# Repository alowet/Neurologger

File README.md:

## WILD: Wireless, Interactive, Lightweight Datalogger 

**WILD** (Wireless, Interactive, Lightweight Datalogger) is an open-source platform for **wireless, closed-loop electrophysiology and behavior monitoring** in freely moving small animals. It integrates high-density electrophysiology, optogenetic stimulation, an inertial measurement unit (IMU), ultrasonic microphone, and head-mounted camera into a lightweight system for **multi-modal recording**.

---

## 📌 Overview

- High-density neural recording  
- BLE-based wireless control and real-time monitoring  
- Closed-loop stimulation with DSP filtering and thresholds  
- SD-card logging in CE32 format with efficient data export  
- Windows GUI for device setup, live visualization, and data download  

---

## 📖 Documentation

Full documentation can be found here:

- [Installation](docs/install.md)  
- [Hardware](docs/hardware.md)
- [Usage Guide](docs/usage.md)  
- [Closed-loop Control](docs/closed-loop.md)
- [TinyML(Under development for supporting user-compiled models)](docs/tinyML.md)
- [File Format](docs/file-format.md)  
- [Development](docs/development.md)  

---

## 🖥 Quick start guide
WILD system board

Connector definitions

WILD system diagram

### Device manufacturing
- PCB manufacturing and assembly (Gerber + BOM provided)
[Download here](https://github.com/ayalab1/Neurologger/tree/main/PCB)  
- Recommended PCB manufacturer: [NextPCB](https://www.nextpcb.com)
- 3D printed baseplate:   [Download here](https://github.com/ayalab1/Neurologger/tree/main/3Dprint)  

### Firmware programming (first time to empty MCU)
1. Connect 4-pin IO–USB cable (do not connect to PC yet).  
2. Short DFU model select pin to VDD(with a metal tweezer for shorting) to enter DFU mode.  
3. Connect USB cable to PC while shorting VDD and model select pin, once powered up, you can release the tweezer.  
4. In **STM32CubeProgrammer**, flash the bootloader firmware.  

### Preparing for recording
- Install WILD PC software:  
  [Download here](https://github.com/ayalab1/Neurologger/tree/main/Software)  
- Format microSD card in WILD PC software (CE32 format).
- Upload application image to SDcard, device will automatically upgrade during power-on from SDcard.
  [Download here](https://github.com/ayalab1/Neurologger/tree/main/Firmware)  
- Ensure battery is fully charged (check polarity on JST-SH2.0 connector).  

### Recording
- Ensure PC has Bluetooth 4.0+ enabled.  
- Connect wirelessly through GUI.  
- Start recording and monitor signals in real time.  

### Data downloading
- Use GUI **Download** function.  
- Files exported as: `amplifier.dat`, `analogin.dat`, `digitalin.dat`, `supply.dat`, `adc.dat`, `time.dat`, `info.rhd`, `CE_params.bin`.  
- Post-processing scripts including data formatting, video generation, sensor-fusions are provided.
[Download here](https://github.com/ayalab1/Neurologger/tree/main/Code)  
---

## ⚠️ Disclaimer

> DISCLAIMER – FOR INFORMATIONAL PURPOSES ONLY; USE AT YOUR OWN RISK  
>  
> The protocol content here is for informational purposes only and does not constitute legal, medical, clinical, or safety advice. Content added to protocols.io is not peer reviewed and may not have undergone formal approval. Information presented should not substitute for independent professional judgment. Any action you take using this information is strictly at your own risk. Neither the authors nor contributors are responsible for your use of the information.

---

## 🔧 Resources

- **Firmware & Embedded software**: Keil MDK, STM32CubeProgrammer  
- **PC GUI / API**: Visual Studio (C#)  
- **Machine learning integration**: Python, TensorFlow, ST Edge-AI  

---

## 📜 License

MIT License. See [LICENSE](LICENSE).

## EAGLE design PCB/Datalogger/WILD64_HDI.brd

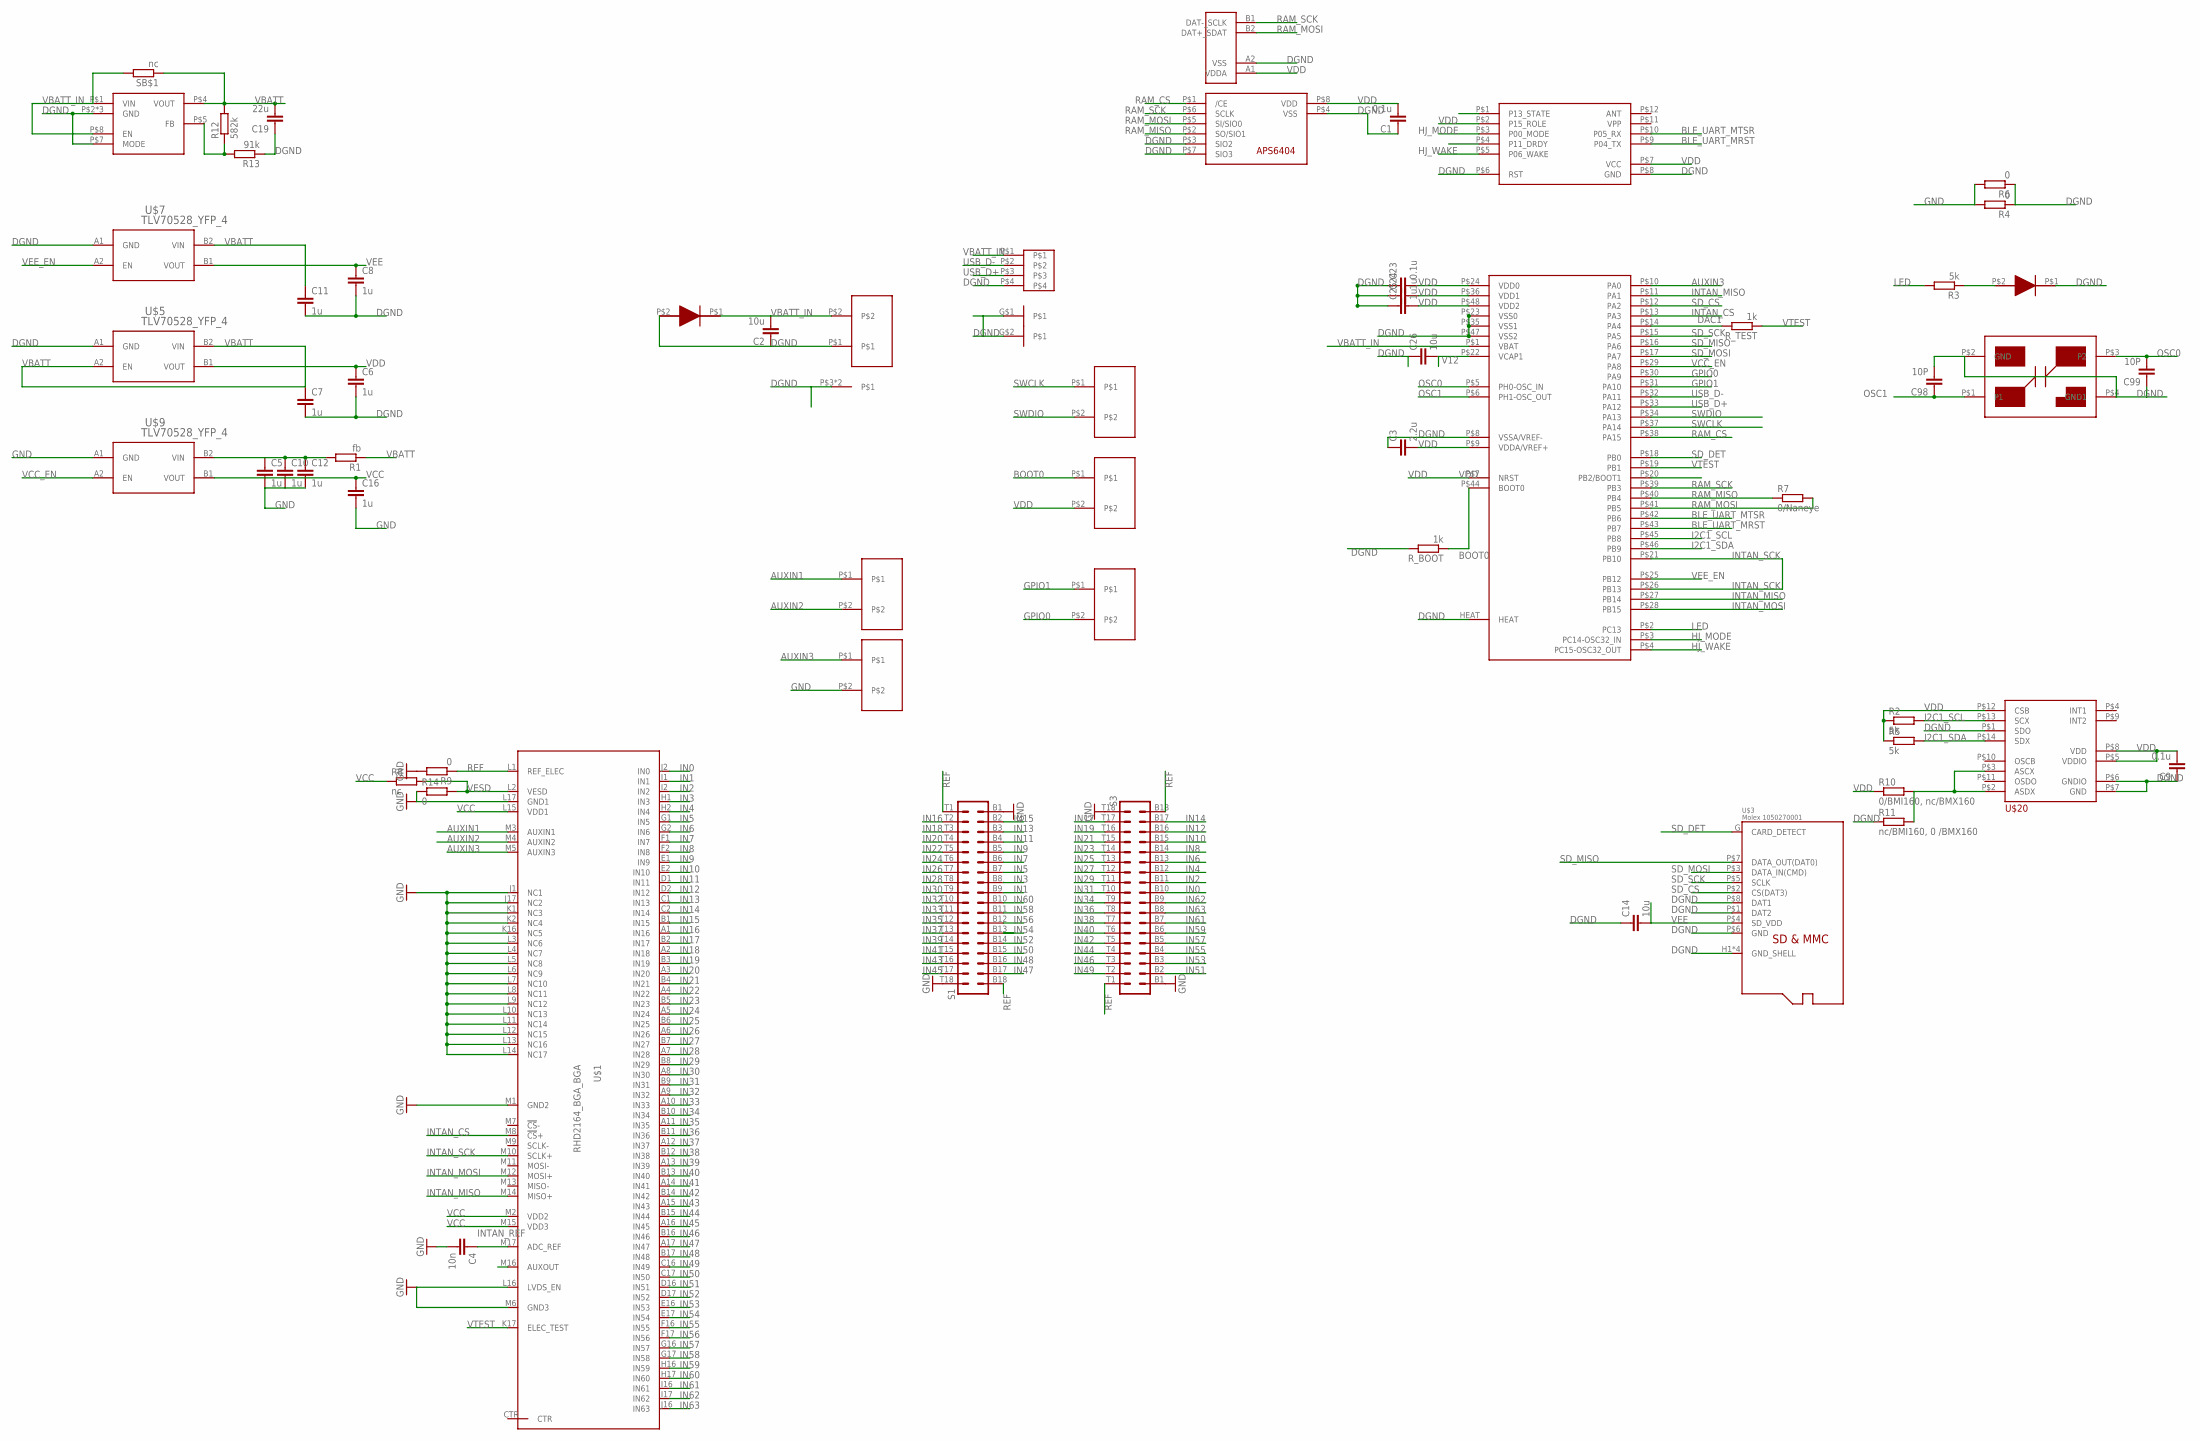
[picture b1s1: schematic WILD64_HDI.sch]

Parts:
C1, C9, C23: 0.1u; C0201
C2: 10u; 0402
C3: 2.2u; C0201
C4: 10n; C0201
C5, C6, C7, C8, C10, C11, C12, C16, C24, C25: 1u; C0201
C14, C26: 10u; C0402
C19: 22u; 0402
C98, C99: 10P; C0201
R1: fb; R0201
R2, R3, R5: 5k; R0201
R4, R6, R14: 0; R0201
R7: 0/Naneye; R0201
R8: nc; R0201
R9: 0; R0402
R10: 0/BMI160, nc/BMX160; R0201
R11: nc/BMI160, 0 /BMX160; R0201
R12: 582k; R0201
R13: 91k; R0201
R_BOOT: 1k; R0201
R_TEST: 1k; R0201
S1, S3: OMNETICS_A79025
SB$1: nc; R0201
U$1: RHD2164_BGA_BGA; BGA104_9X7
U$2: 1.0MM_1X2VIA; PIN_1.0MM_1X2
U$3: Molex 1050270001; MICROSD_SHORT_1.7H
U$4: NANEYECBGA; NANEYEC_4BGA
U$5, U$7, U$9: TLV70528_YFP_4; YFP4
U$6: STM32F411_QFN48; UFQFPN48
U$8, U$17, U$18, U$19: 1.27MM_1X2CONN; 1.27MM_1X2
U$10: HJ580
U$11, U$16: DIODE0402; 0402_LED
U$12: 1.0MM_1X4PAD; 1.0MM_CONN_1X4_SMD
U$13: 1.00MM_1X2PAD; 1.0MM_CONN_1X2_SMD
U$14: APS6404; USON-8L_3X2
U$15: ABM12_CRYSTAL; SMD4_1.6MMX1.2MM
U$20: BMI27014; 14_VFLGA
U$22: TPSM83100; MICROSIP_SIU0008A

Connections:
AUXIN1: U$1.M3 (AUXIN1), U$19.P$1
AUXIN2: U$1.M4 (AUXIN2), U$19.P$2
AUXIN3: U$1.M5 (AUXIN3), U$6.P$10 (PA0), U$18.P$1
AUXOUT: U$1.M16 (AUXOUT)
BLE_UART_MRST: U$6.P$43 (PB7), U$10.P$9 (P04_TX)
BLE_UART_MTSR: U$6.P$42 (PB6), U$10.P$10 (P05_RX)
BOOT0: R_BOOT.1, U$6.P$44 (BOOT0), U$8.P$1
DAC1: R_TEST.2, U$6.P$14 (PA4)
DGND: C1.1, C2.1, C3.1, C6.2, C7.2, C8.2, C9.1, C11.2, C14.1, C19.1, C23.1, C24.1, C25.1, C26.1, C98.2, C99.1, R4.1, R6.1, R11.1, R13.1, R_BOOT.2, U$3.H1 (GND_SHELL), U$3.H2 (GND_SHELL), U$3.H3 (GND_SHELL), U$3.H4 (GND_SHELL), U$3.P$1 (DAT2), U$3.P$6 (GND), U$3.P$8 (DAT1), U$4.A2 (VSS), U$5.A1 (GND), U$6.HEAT, U$6.P$8 (VSSA/VREF-), U$6.P$23 (VSS0), U$6.P$35 (VSS1), U$6.P$47 (VSS2), U$7.A1 (GND), U$10.P$6 (RST), U$10.P$8 (GND), U$11.P$2 (IN), U$12.G$1, U$12.G$2, U$12.P$4, U$13.P$1, U$13.P$3, U$13.P$4, U$14.P$3 (SIO2), U$14.P$4 (VSS), U$14.P$7 (SIO3), U$15.P$2 (GND), U$15.P$4 (GND1), U$16.P$1 (OUT), U$20.P$1 (SDO), U$20.P$6 (GNDIO), U$20.P$7 (GND), U$22.P$2 (GND), U$22.P$3 (GND), U$22.P$6 (GND), U$22.P$7 (MODE)
GND: C4.2, C5.2, C10.2, C12.2, C16.2, R4.2, R6.2, R9.2, R14.1, S1.B1, S1.T18, S3.B1, S3.T18, U$1.J1 (NC1), U$1.J17 (NC2), U$1.K1 (NC3), U$1.K2 (NC4), U$1.K16 (NC5), U$1.L3 (NC6), U$1.L4 (NC7), U$1.L5 (NC8), U$1.L6 (NC9), U$1.L7 (NC10), U$1.L8 (NC11), U$1.L9 (NC12), U$1.L10 (NC13), U$1.L11 (NC14), U$1.L12 (NC15), U$1.L13 (NC16), U$1.L14 (NC17), U$1.L16 (LVDS_EN), U$1.L17 (GND1), U$1.M1 (GND2), U$1.M6 (GND3), U$9.A1 (GND), U$18.P$2
GPIO0: U$6.P$30 (PA9), U$17.P$2
GPIO1: U$6.P$31 (PA10), U$17.P$1
HJ_MODE: U$6.P$3 (PC14-OSC32_IN), U$10.P$3 (P00_MODE)
HJ_WAKE: U$6.P$4 (PC15-OSC32_OUT), U$10.P$5 (P06_WAKE)
I2C1_SCL: R2.2, U$6.P$45 (PB8), U$20.P$13 (SCX)
I2C1_SDA: R5.2, U$6.P$46 (PB9), U$20.P$14 (SDX)
IN0: S3.B10, U$1.J2 (IN0)
IN1: S1.B9, U$1.I1 (IN1)
IN2: S3.B11, U$1.I2 (IN2)
IN3: S1.B8, U$1.H1 (IN3)
IN4: S3.B12, U$1.H2 (IN4)
IN5: S1.B7, U$1.G1 (IN5)
IN6: S3.B13, U$1.G2 (IN6)
IN7: S1.B6, U$1.F1 (IN7)
IN8: S3.B14, U$1.F2 (IN8)
IN9: S1.B5, U$1.E1 (IN9)
IN10: S3.B15, U$1.E2 (IN10)
IN11: S1.B4, U$1.D1 (IN11)
IN12: S3.B16, U$1.D2 (IN12)
IN13: S1.B3, U$1.C1 (IN13)
IN14: S3.B17, U$1.C2 (IN14)
IN15: S1.B2, U$1.B1 (IN15)
IN16: S1.T2, U$1.A1 (IN16)
IN17: S3.T17, U$1.B2 (IN17)
IN18: S1.T3, U$1.A2 (IN18)
IN19: S3.T16, U$1.B3 (IN19)
IN20: S1.T4, U$1.A3 (IN20)
IN21: S3.T15, U$1.B4 (IN21)
IN22: S1.T5, U$1.A4 (IN22)
IN23: S3.T14, U$1.B5 (IN23)
IN24: S1.T6, U$1.A5 (IN24)
IN25: S3.T13, U$1.B6 (IN25)
IN26: S1.T7, U$1.A6 (IN26)
IN27: S3.T12, U$1.B7 (IN27)
IN28: S1.T8, U$1.A7 (IN28)
IN29: S3.T11, U$1.B8 (IN29)
IN30: S1.T9, U$1.A8 (IN30)
IN31: S3.T10, U$1.B9 (IN31)
IN32: S1.T10, U$1.A9 (IN32)
IN33: S1.T11, U$1.A10 (IN33)
IN34: S3.T9, U$1.B10 (IN34)
IN35: S1.T12, U$1.A11 (IN35)
IN36: S3.T8, U$1.B11 (IN36)
IN37: S1.T13, U$1.A12 (IN37)
IN38: S3.T7, U$1.B12 (IN38)
IN39: S1.T14, U$1.A13 (IN39)
IN40: S3.T6, U$1.B13 (IN40)
IN41: S1.T15, U$1.A14 (IN41)
IN42: S3.T5, U$1.B14 (IN42)
IN43: S1.T16, U$1.A15 (IN43)
IN44: S3.T4, U$1.B15 (IN44)
IN45: S1.T17, U$1.A16 (IN45)
IN46: S3.T3, U$1.B16 (IN46)
IN47: S1.B17, U$1.A17 (IN47)
IN48: S1.B16, U$1.B17 (IN48)
IN49: S3.T2, U$1.C16 (IN49)
IN50: S1.B15, U$1.C17 (IN50)
IN51: S3.B2, U$1.D16 (IN51)
IN52: S1.B14, U$1.D17 (IN52)
IN53: S3.B3, U$1.E16 (IN53)
IN54: S1.B13, U$1.E17 (IN54)
IN55: S3.B4, U$1.F16 (IN55)
IN56: S1.B12, U$1.F17 (IN56)
IN57: S3.B5, U$1.G16 (IN57)
IN58: S1.B11, U$1.G17 (IN58)
IN59: S3.B6, U$1.H16 (IN59)
IN60: S1.B10, U$1.H17 (IN60)
IN61: S3.B7, U$1.I16 (IN61)
IN62: S3.B9, U$1.I17 (IN62)
IN63: S3.B8, U$1.J16 (IN63)
INTAN_CS: U$1.M8 (!CS!+), U$6.P$13 (PA3)
INTAN_MISO: U$1.M14 (MISO+), U$6.P$11 (PA1), U$6.P$27 (PB14)
INTAN_MOSI: U$1.M12 (MOSI+), U$6.P$28 (PB15)
INTAN_REF: C4.1, U$1.M17 (ADC_REF)
INTAN_SCK: U$1.M10 (SCLK+), U$6.P$21 (PB10), U$6.P$26 (PB13)
LED: R3.2, U$6.P$2 (PC13)
unnamed: R10.2, R11.2, U$20.P$2 (ASDX), U$20.P$3 (ASCX)
unnamed: R12.1, R13.2, U$22.P$5 (FB)
unnamed: R3.1, U$16.P$2 (IN)
OSC0: C99.2, U$6.P$5 (PH0-OSC_IN), U$15.P$3 (P2)
OSC1: C98.1, U$6.P$6 (PH1-OSC_OUT), U$15.P$1 (P1)
RAM_CS: U$6.P$38 (PA15), U$14.P$1 (/CE)
RAM_MISO: R7.1, U$6.P$40 (PB4), U$14.P$2 (SO/SIO1)
RAM_MOSI: R7.2, U$4.B2 (DAT+_SDAT), U$6.P$41 (PB5), U$14.P$5 (SI/SIO0)
RAM_SCK: U$4.B1 (DAT-_SCLK), U$6.P$39 (PB3), U$14.P$6 (SCLK)
REF: R9.1, S1.B18, S1.T1, S3.B18, S3.T1, U$1.L1 (REF_ELEC)
SD_CS: U$3.P$2 (CS(DAT3)), U$6.P$12 (PA2)
SD_DET: U$3.G (CARD_DETECT), U$6.P$18 (PB0)
SD_MISO: U$3.P$7 (DATA_OUT(DAT0)), U$6.P$16 (PA6)
SD_MOSI: U$3.P$3 (DATA_IN(CMD)), U$6.P$17 (PA7)
SD_SCK: U$3.P$5 (SCLK), U$6.P$15 (PA5)
SWCLK: U$2.P$1, U$6.P$37 (PA14)
SWDIO: U$2.P$2, U$6.P$34 (PA13)
USB_D+: U$6.P$33 (PA12), U$12.P$3
USB_D-: U$6.P$32 (PA11), U$12.P$2
V12: C26.2, U$6.P$22 (VCAP1)
VBATT: C7.1, C11.1, C19.2, R1.1, R12.2, SB$1.1, U$5.A2 (EN), U$5.B2 (VIN), U$7.B2 (VIN), U$22.P$4 (VOUT)
VBATT_IN: C2.2, SB$1.2, U$6.P$1 (VBAT), U$11.P$1 (OUT), U$12.P$1, U$13.P$2, U$22.P$1 (VIN), U$22.P$8 (EN)
VCC: C16.1, R8.1, U$1.L15 (VDD1), U$1.M2 (VDD2), U$1.M15 (VDD3), U$9.B1 (VOUT)
VCC_EN: U$6.P$29 (PA8), U$9.A2 (EN)
VCC_LPF: C5.1, C10.1, C12.1, R1.2, U$9.B2 (VIN)
VDD: C1.2, C3.2, C6.1, C9.2, C23.2, C24.2, C25.2, R2.1, R5.1, R10.1, U$4.A1 (VDDA), U$5.B1 (VOUT), U$6.P$7 (NRST), U$6.P$9 (VDDA/VREF+), U$6.P$24 (VDD0), U$6.P$36 (VDD1), U$6.P$48 (VDD2), U$8.P$2, U$10.P$2 (P15_ROLE), U$10.P$7 (VCC), U$14.P$8 (VDD), U$20.P$5 (VDDIO), U$20.P$8 (VDD), U$20.P$12 (CSB)
VEE: C8.1, C14.2, U$3.P$4 (SD_VDD), U$7.B1 (VOUT)
VEE_EN: U$6.P$25 (PB12), U$7.A2 (EN)
VESD: R8.2, R14.2, U$1.L2 (VESD)
VTEST: R_TEST.1, U$1.K17 (ELEC_TEST), U$6.P$19 (PB1)

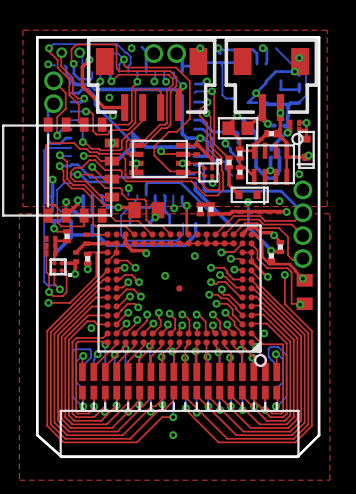
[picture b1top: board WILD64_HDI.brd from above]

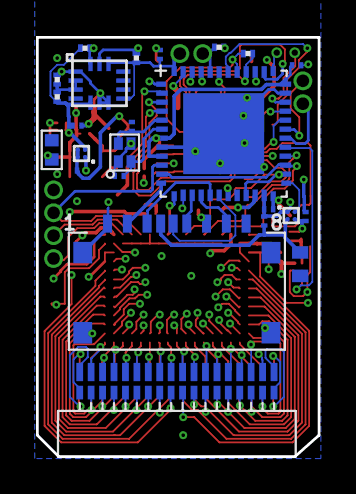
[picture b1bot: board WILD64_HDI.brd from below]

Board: 4 copper layers, 15.7 x 23.3 mm, 61 parts (26 on the bottom side), 115 nets.

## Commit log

2025-09-21 PCB manufactoring file uploads
2025-09-21 Software, test firmware uploaded
2025-09-21 3D print file submitted
2025-09-29 Push multi-page documentations
2025-09-29 Upload data processing scripts
2025-09-29 Image test
2025-09-29 Add ! to show image
2025-09-29 Updated documents
2025-09-29 Adding documents
2025-09-29 Added more photos
2025-09-29 Edited fileformat
2025-09-29 Added camera mode application file
2025-09-29 Updated WILD-API for correct WILD64X data downloading
2025-09-30 uploaded missing matlab dependencies
2025-09-30 removed excess .zip file
2025-09-30 EaglePCB files of datalogger uploaded
2025-10-01 corrected naming for functions to wild; simplified data path handling
2025-10-01 Updated missing matlab dependencies
2025-10-01 Channel map uploaded
2025-10-01 Updated battery for usage
2025-10-01 Updated power consumption of sd card and lithium battery list
2025-10-01 Added bootloader image for initial DFU programming
2025-10-01 Added opto-module firmware image (need to program through SWD interface(St-link)
2025-10-08 Upload original designs of 3D print case
2025-10-10 Fixed a bug that saves a unrecognizable firmware version during FW update
2025-10-11 Added pre-processing support for CE64X file format, improved pre-processing logics
    Ignored digin signal with all 1s
    Added rec_time in matlab datetime format in WILD_Readheader.
    Decode CE64X format correctly
2025-10-11 Update WILD_PreProcess.m
    removed dependencies on d14 signal
2025-10-16 3D print files for CambridgeNT
